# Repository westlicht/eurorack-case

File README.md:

Some design files for custom eurorack case and multiples row.

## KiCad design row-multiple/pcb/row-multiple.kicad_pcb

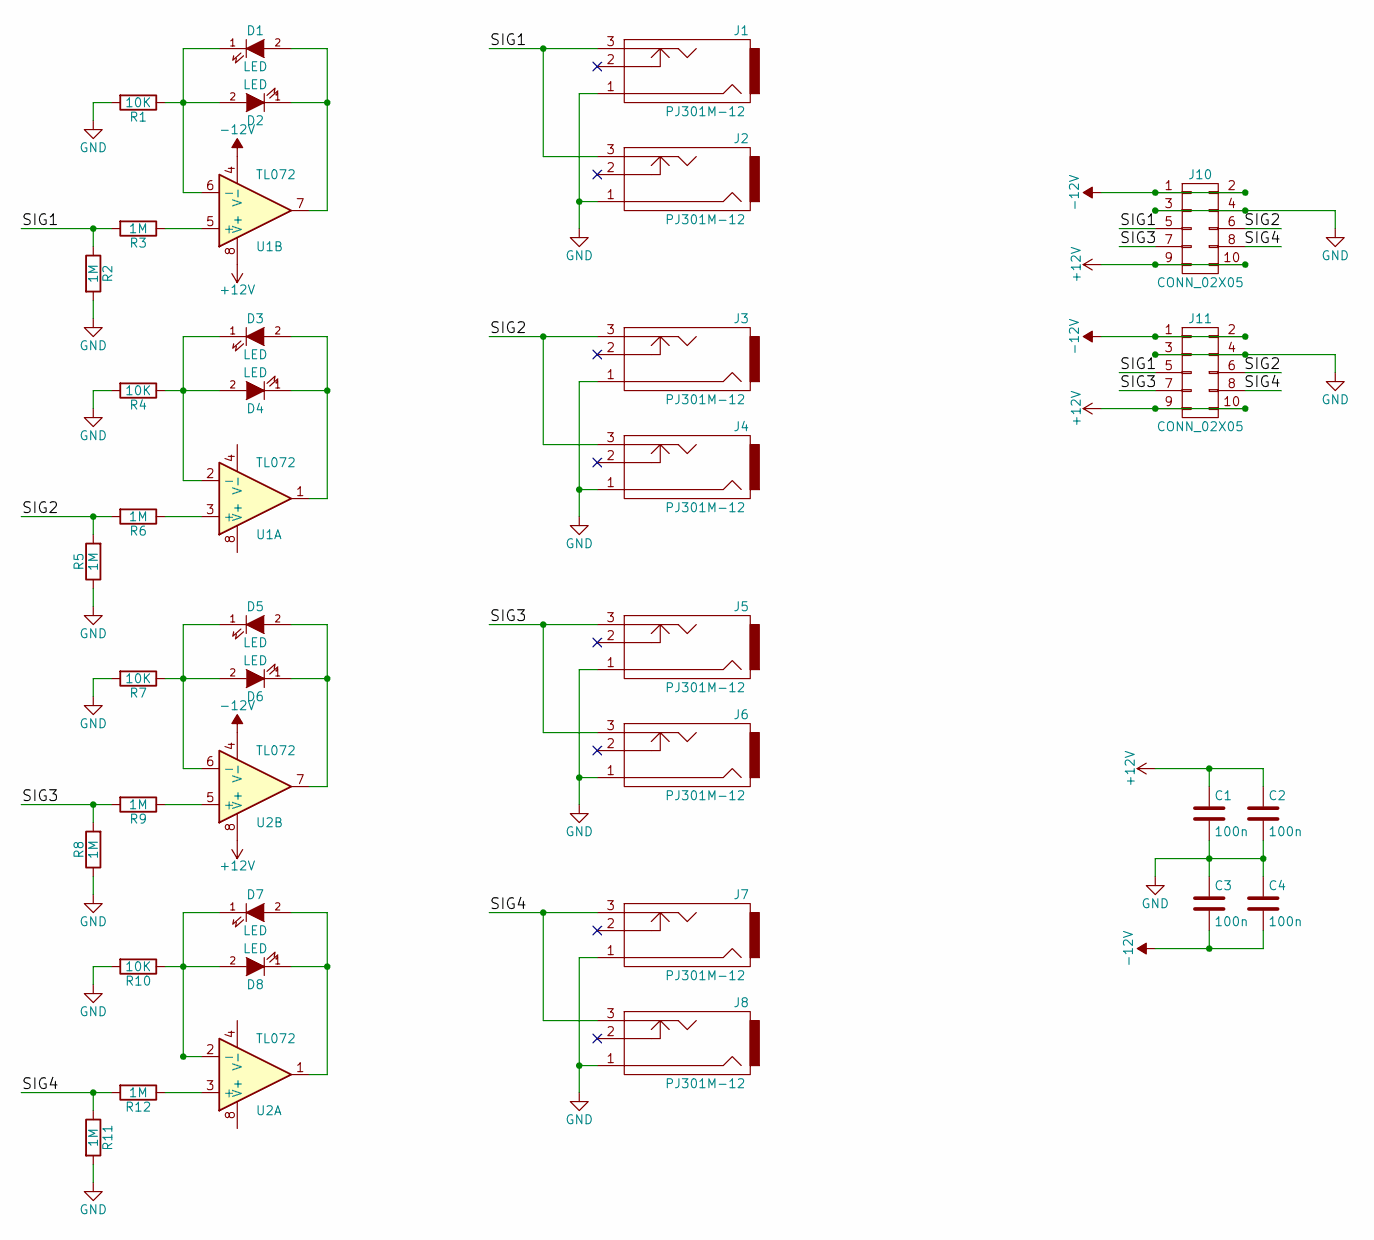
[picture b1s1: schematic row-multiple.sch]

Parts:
C1, C2, C3, C4: 100n; C_0603_HandSoldering
D1, D2, D3, D4, D5, D6, D7, D8: LED; LED_D3.0mm
J1, J2, J3, J4, J5, J6, J7, J8: PJ301M-12
J10, J11: CONN_02X05; Pin_Header_Straight_2x05_Pitch2.54mm
R1, R4, R7, R10: 10K; R_0603_HandSoldering
R2, R3, R5, R6, R8, R9, R11, R12: 1M; R_0603_HandSoldering
U1, U2: TL072; SOIC-8-N

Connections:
+12V: C1.1, C2.1, J10.9, J10.10, J11.9, J11.10, U1.8 (V+), U2.8 (V+)
-12V: C3.2, C4.2, J10.1, J10.2, J11.1, J11.2, U1.4 (V-), U2.4 (V-)
/SIG1: J1.3, J2.3, J10.5, J11.5, R2.1, R3.2
/SIG2: J3.3, J4.3, J10.6, J11.6, R5.2, R6.2
/SIG3: J5.3, J6.3, J10.7, J11.7, R8.2, R9.2
/SIG4: J7.3, J8.3, J10.8, J11.8, R11.1, R12.2
GND: C1.2, C2.2, C3.1, C4.1, J1.1, J2.1, J3.1, J4.1, J5.1, J6.1, J7.1, J8.1, J10.3, J10.4, J11.3, J11.4, R1.2, R2.2, R4.2, R5.1, R7.2, R8.1, R10.2, R11.2
unnamed: D1.1 (K), D2.2 (A), R1.1, U1.6 (-)
unnamed: D1.2 (A), D2.1 (K), U1.7
unnamed: D3.1 (K), D4.2 (A), R4.1, U1.2 (-)
unnamed: D3.2 (A), D4.1 (K), U1.1
unnamed: D5.1 (K), D6.2 (A), R7.1, U2.6 (-)
unnamed: D5.2 (A), D6.1 (K), U2.7
unnamed: D7.1 (K), D8.2 (A), R10.1, U2.2 (-)
unnamed: D7.2 (A), D8.1 (K), U2.1
unnamed: R3.1, U1.5 (+)
unnamed: R6.1, U1.3 (+)
unnamed: R9.1, U2.5 (+)
unnamed: R12.1, U2.3 (+)

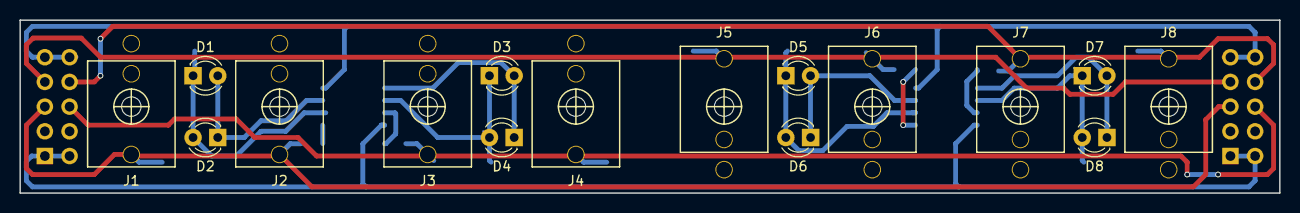
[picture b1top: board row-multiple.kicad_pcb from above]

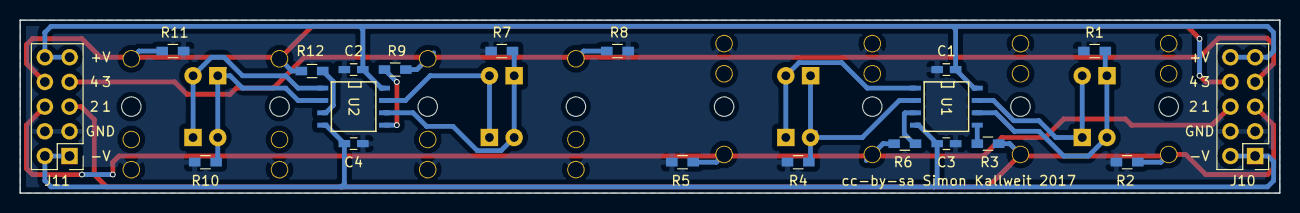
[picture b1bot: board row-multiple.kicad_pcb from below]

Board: 2 copper layers, 129.5 x 17.8 mm, 36 parts (20 on the bottom side), 19 nets.

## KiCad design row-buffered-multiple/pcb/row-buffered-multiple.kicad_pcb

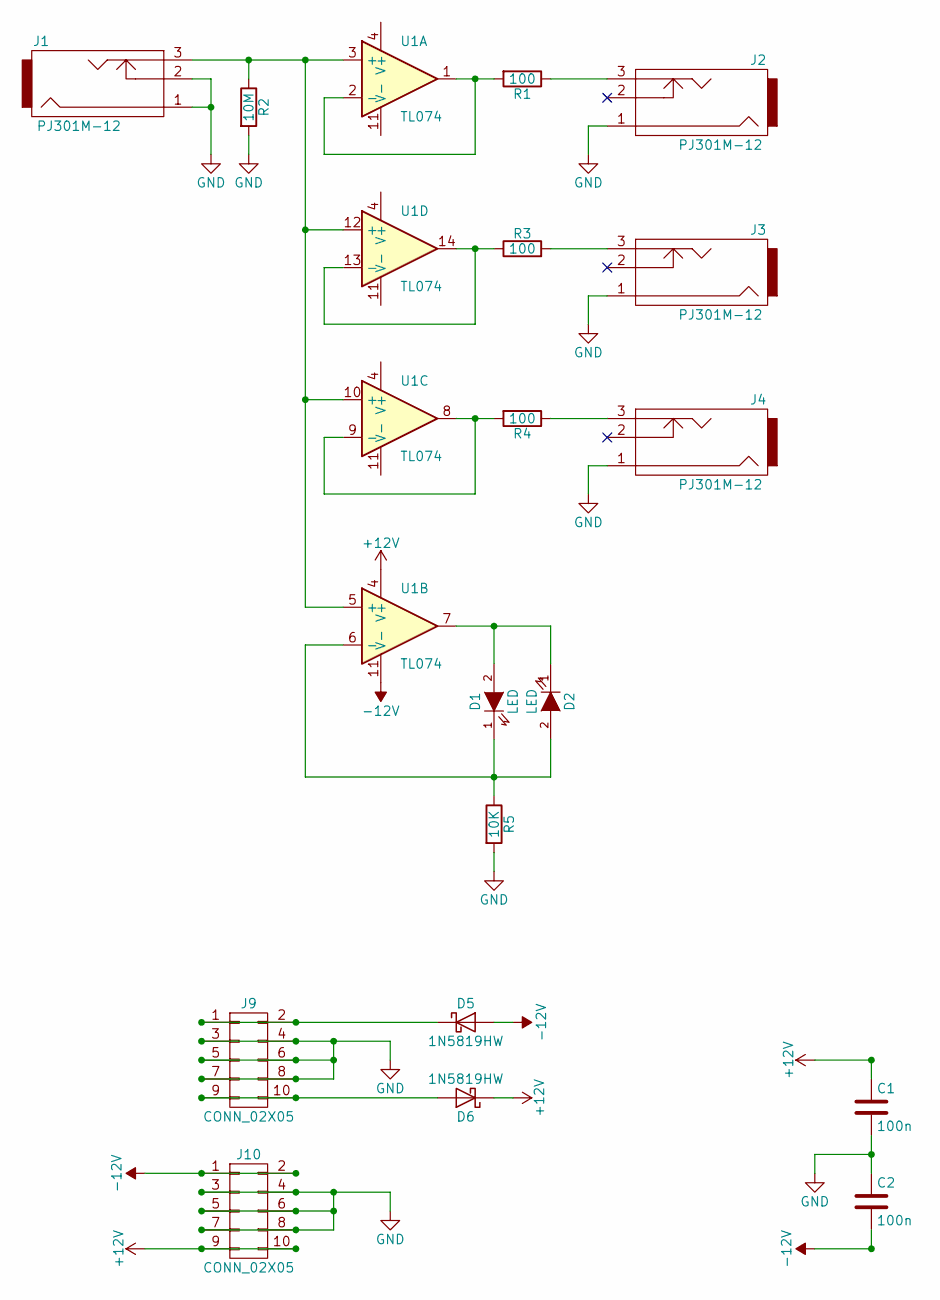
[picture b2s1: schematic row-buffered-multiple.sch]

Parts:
C1, C2: 100n; C_0603_HandSoldering
D1, D2: LED; LED_D3.0mm
D5, D6: 1N5819HW; D_SOD-123
J1, J2, J3, J4: PJ301M-12
J9, J10: CONN_02X05; Pin_Header_Straight_2x05_Pitch2.54mm
R1, R3, R4: 100; R_0603_HandSoldering
R2: 10M; R_0603_HandSoldering
R5: 10K; R_0603_HandSoldering
U1: TL074; SOIC-14_N

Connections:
+12V: C1.1, D6.1 (K), J10.9, J10.10, U1.4 (V+)
-12V: C2.2, D5.2 (A), J10.1, J10.2, U1.11 (V-)
GND: C1.2, C2.1, J1.1, J1.2, J2.1, J3.1, J4.1, J9.3, J9.4, J9.5, J9.6, J9.7, J9.8, J10.3, J10.4, J10.5, J10.6, J10.7, J10.8, R2.2, R5.2
unnamed: D1.1 (K), D2.2 (A), R5.1, U1.6 (-)
unnamed: D1.2 (A), D2.1 (K), U1.7
unnamed: D5.1 (K), J9.1, J9.2
unnamed: D6.2 (A), J9.9, J9.10
unnamed: J1.3, R2.1, U1.3 (+), U1.5 (+), U1.10 (+), U1.12 (+)
unnamed: J2.3, R1.1
unnamed: J3.3, R3.2
unnamed: J4.3, R4.1
unnamed: R1.2, U1.1, U1.2 (-)
unnamed: R3.1, U1.13 (-), U1.14
unnamed: R4.2, U1.8, U1.9 (-)

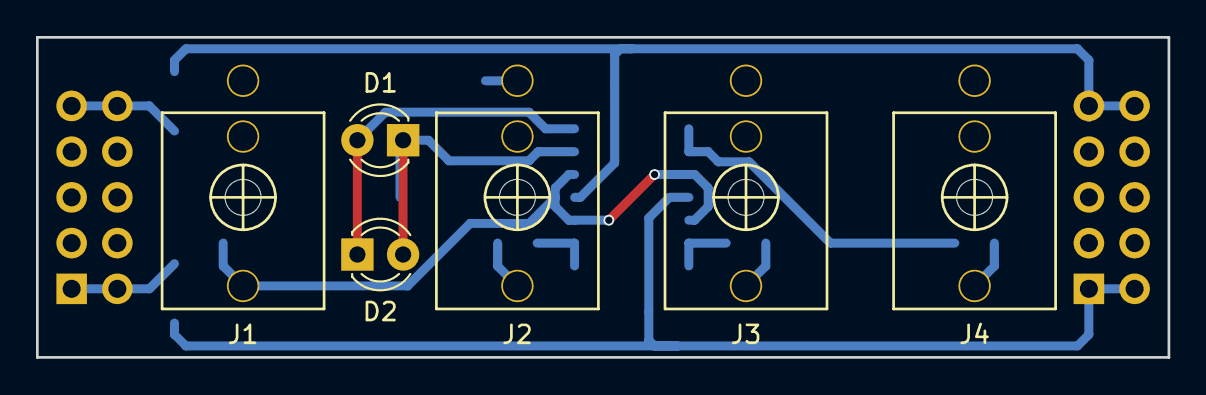
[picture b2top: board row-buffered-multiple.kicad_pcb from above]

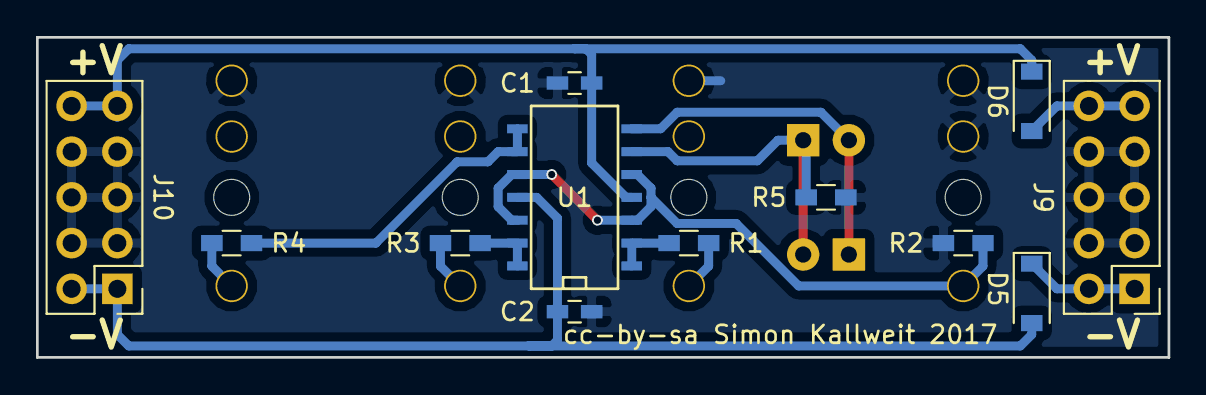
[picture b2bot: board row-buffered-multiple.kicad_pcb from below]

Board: 2 copper layers, 62.9 x 17.8 mm, 18 parts (12 on the bottom side), 14 nets.

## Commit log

2018-09-29 initial import
2018-09-29 forked eurocad repo
2018-09-29 updated library submodules

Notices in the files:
row-buffered-multiple/pcb/row-buffered-multiple.kicad_pcb:
cc-by-sa Simon Kallweit 2017
